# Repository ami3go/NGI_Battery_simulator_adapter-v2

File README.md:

# NGI_Battery_simulator_adapter-v2
 Simple PCB adapter for easy wiring from sell cimulator to load

 Features: 
 - Power wirse +  sensign wires
 - Optional NTC emulation
 - 3.5 mm universal connector
 - Additioan connector for extnal measurement device
 - cable ties holes to fix bulky wires

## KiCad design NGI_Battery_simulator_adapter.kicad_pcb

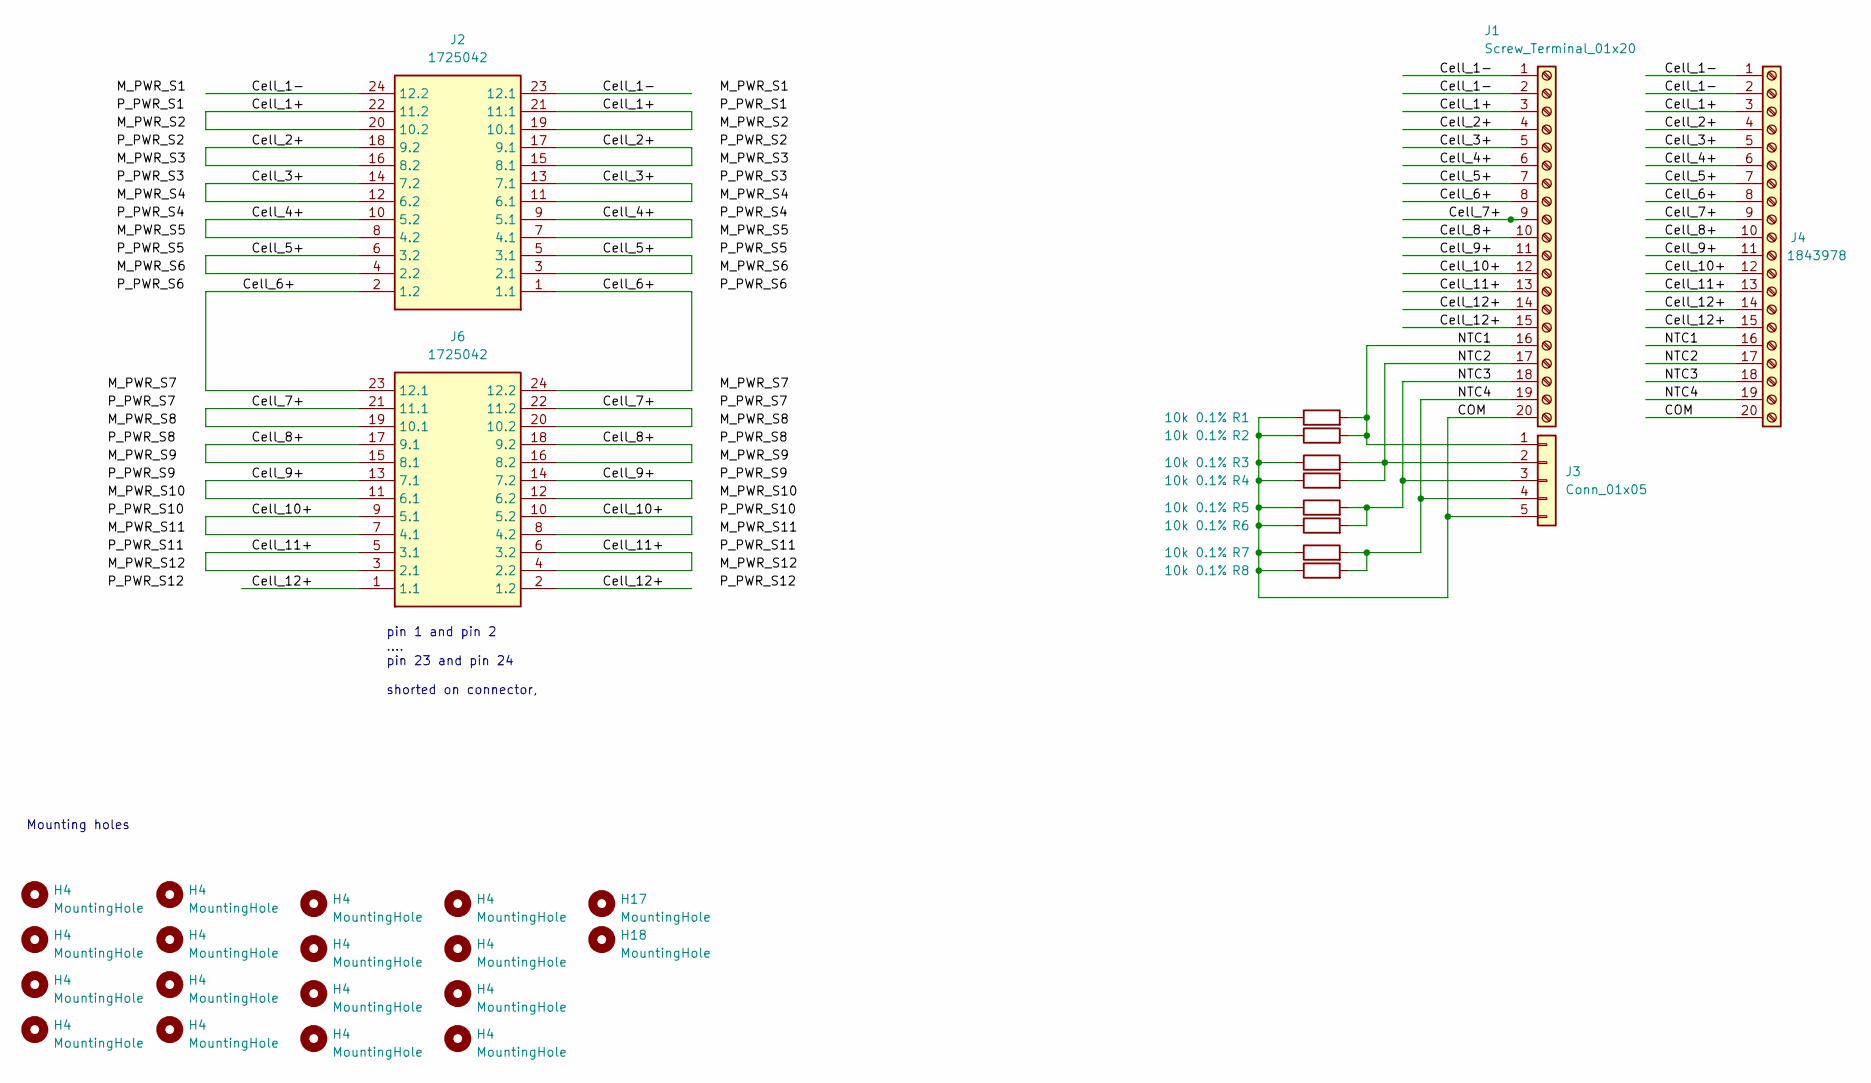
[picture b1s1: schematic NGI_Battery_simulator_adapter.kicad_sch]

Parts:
H4, H17, H18: MountingHole; MountingHole_3.2mm_M3_ISO14580
J1: Screw_Terminal_01x20; TerminalBlock_4Ucon_1x20_P3.50mm_Vertical_copy
J2, J6: 1725042; Manufacturer_Part_Number 1725042; Mouser Part Number 651-1725042
J3: Conn_01x05; PinHeader_1x05_P2.54mm_Vertical
J4: Screw_Terminal_01x20; TerminalBlock_4Ucon_1x20_P3.50mm_horisontal; MPN 1843978
R1, R2, R3, R4, R5, R6, R7, R8: 10k_0603_0.1%; R_0603; Part Number ERJ-PB3B1002V

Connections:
/COM: J1.20, J3.5, J4.20, R1.1, R2.1, R3.1, R4.1, R5.1, R6.1, R7.1, R8.1
/Cell_1+: J1.3, J2.19 (10.1), J2.20 (10.2), J2.21 (11.1), J2.22 (11.2), J4.3
/Cell_1-: J1.1, J1.2, J2.23 (12.1), J2.24 (12.2), J4.1, J4.2
/Cell_2+: J1.4, J2.15 (8.1), J2.16 (8.2), J2.17 (9.1), J2.18 (9.2), J4.4
/Cell_3+: J1.5, J2.11 (6.1), J2.12 (6.2), J2.13 (7.1), J2.14 (7.2), J4.5
/Cell_4+: J1.6, J2.7 (4.1), J2.8 (4.2), J2.9 (5.1), J2.10 (5.2), J4.6
/Cell_5+: J1.7, J2.3 (2.1), J2.4 (2.2), J2.5 (3.1), J2.6 (3.2), J4.7
/Cell_6+: J1.8, J2.1 (1.1), J2.2 (1.2), J4.8, J6.23 (12.1), J6.24 (12.2)
/Cell_7+: J1.9, J4.9, J6.19 (10.1), J6.20 (10.2), J6.21 (11.1), J6.22 (11.2)
/Cell_8+: J1.10, J4.10, J6.15 (8.1), J6.16 (8.2), J6.17 (9.1), J6.18 (9.2)
/Cell_9+: J1.11, J4.11, J6.11 (6.1), J6.12 (6.2), J6.13 (7.1), J6.14 (7.2)
/Cell_10+: J1.12, J4.12, J6.7 (4.1), J6.8 (4.2), J6.9 (5.1), J6.10 (5.2)
/Cell_11+: J1.13, J4.13, J6.3 (2.1), J6.4 (2.2), J6.5 (3.1), J6.6 (3.2)
/Cell_12+: J1.14, J1.15, J4.14, J4.15, J6.1 (1.1), J6.2 (1.2)
/NTC1: J1.16, J3.1, J4.16, R1.2, R2.2
/NTC2: J1.17, J3.2, J4.17, R3.2, R4.2
/NTC3: J1.18, J3.3, J4.18, R5.2, R6.2
/NTC4: J1.19, J3.4, J4.19, R7.2, R8.2

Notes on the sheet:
Mounting holes
pin 1 and pin 2 .... pin 23 and pin 24 shorted on connector,

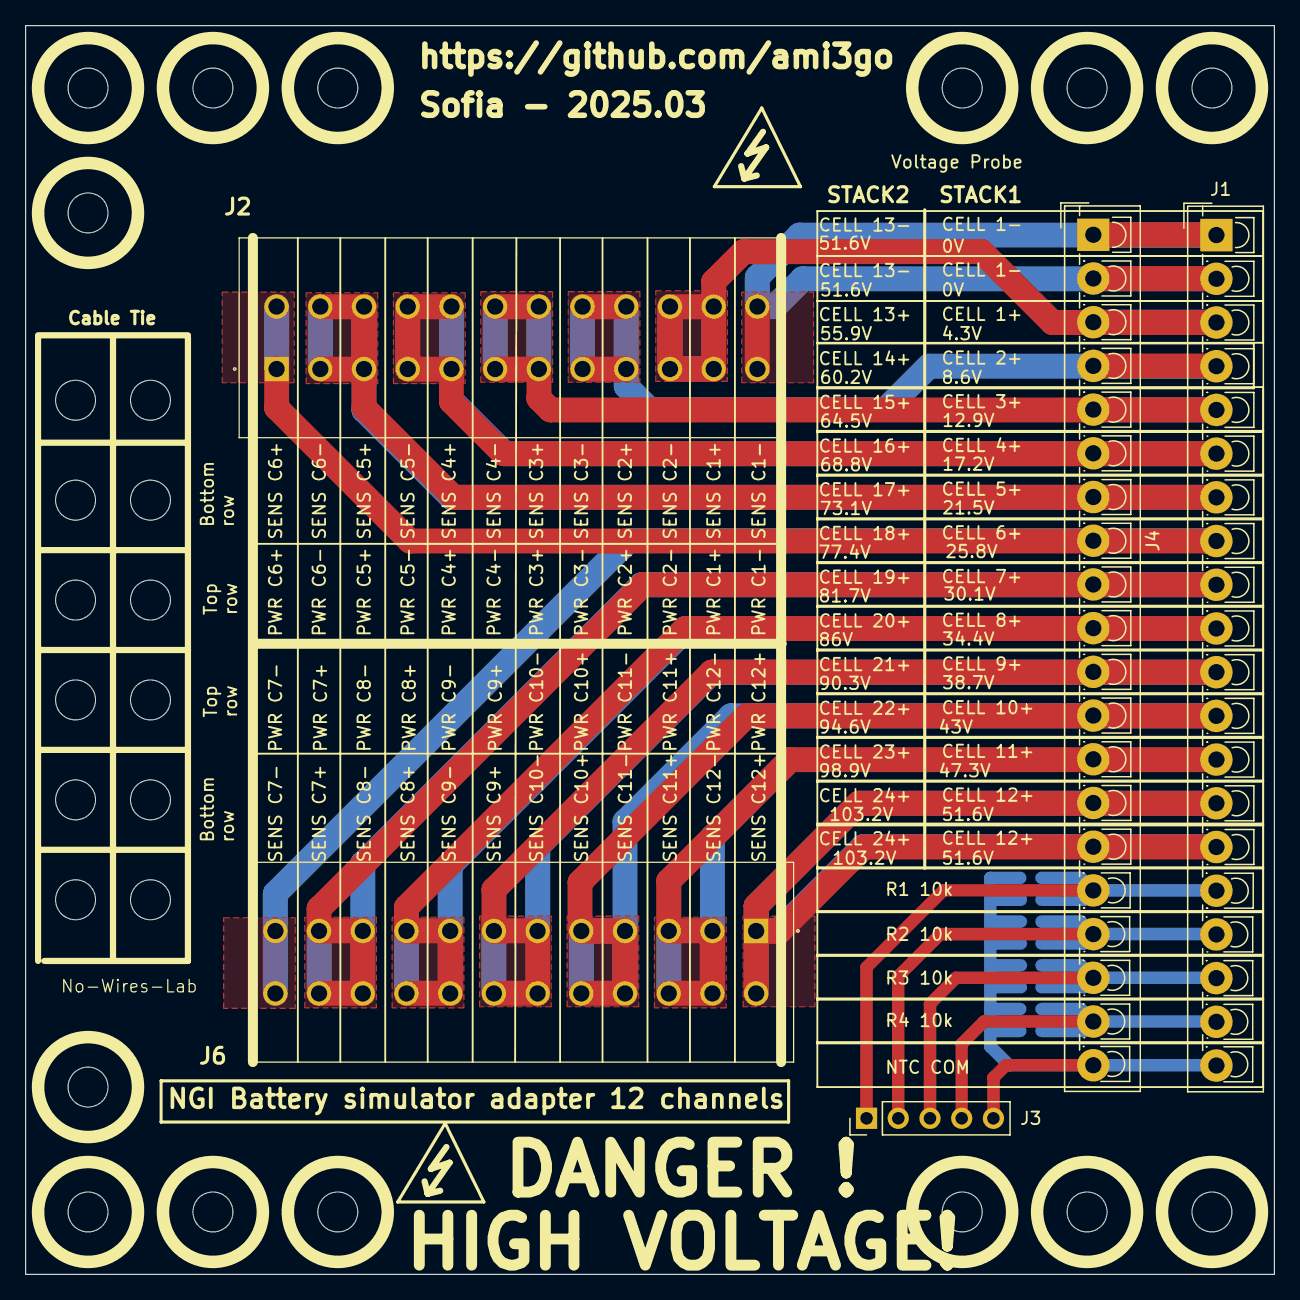
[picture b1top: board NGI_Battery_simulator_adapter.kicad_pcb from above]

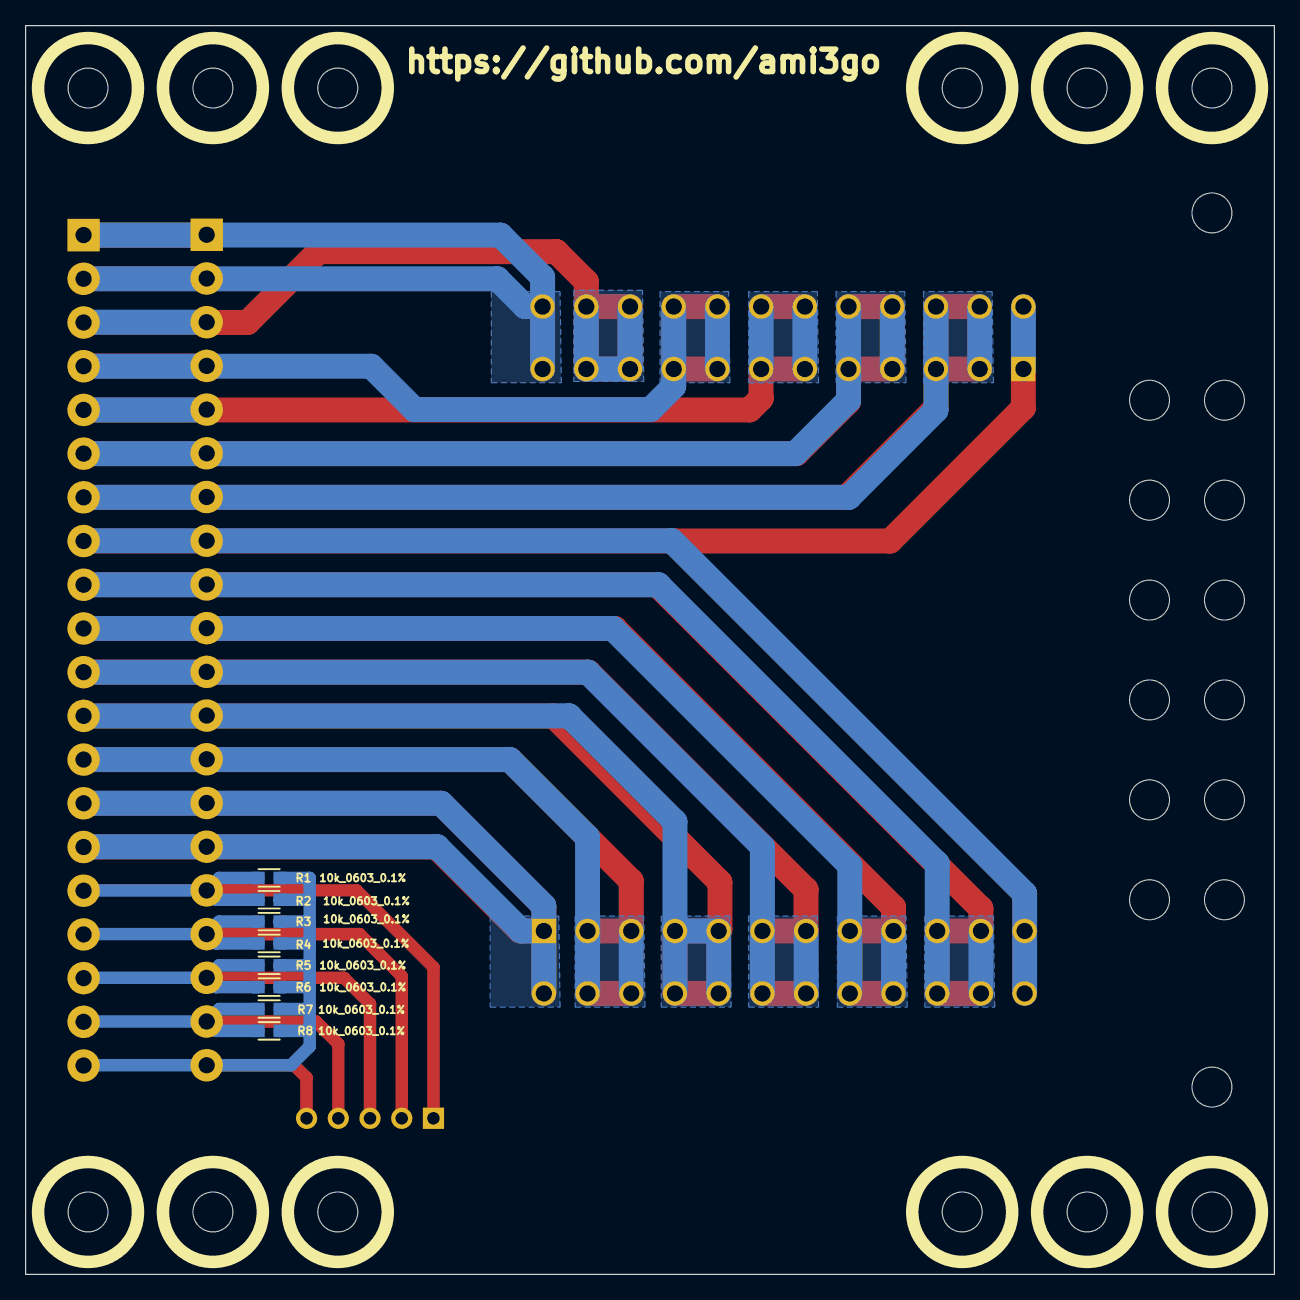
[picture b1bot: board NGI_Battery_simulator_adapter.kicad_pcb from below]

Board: 2 copper layers, 100.0 x 100.0 mm, 39 parts (8 on the bottom side), 18 nets.

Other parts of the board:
H1, H2, H3, H5, H5#2, H5#3, H6, H7, H7#2, H8, H8#2, H8#3, H8#4, H8#5, H8#6, H9, H10, H11, H12, H13, H14, H15, H16: MountingHole; MountingHole_3.2mm_M3_ISO14580

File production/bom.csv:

Designator,Footprint,Quantity,Value,LCSC Part #
"H1, H10, H11, H12, H13, H14, H15, H16, H17, H18, H2, H3, H4, H5_3, H5_2, H5, H6, H7_2, H7, H8_6, H8_5, H8_4, H8_3, H8_2, H8, H9",MountingHole_3.2mm_M3_ISO14580,26,MountingHole,
J1,TerminalBlock_4Ucon_1x20_P3.50mm_Vertical_copy,1,Screw_Terminal_01x20,
"J2, J6",1725042,2,1725042,
J3,PinHeader_1x05_P2.54mm_Vertical,1,Conn_01x05,
J4,TerminalBlock_4Ucon_1x20_P3.50mm_horisontal,1,Screw_Terminal_01x20,1843978
"R1, R2, R3, R4, R5, R6, R7, R8",R_0603,8,10k_0603_0.1%,

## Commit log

2024-01-08 gerber update
    fix some DRC error, minor change
2024-01-10 Update README.md
    Description update
2025-03-17 Clean up back up folder
2025-03-17 update for Kicad 9
2025-03-17 Update gerbers
2025-03-17 Add 3D
2025-03-19 Clean up
2025-03-19 Updated 3D
2025-04-02 3D enclosure work in progress
